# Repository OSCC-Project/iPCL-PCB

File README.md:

# iPCL-PCB

PCB design assets for the iPCL project (OSCC).

## Designs

| File | Description |
|------|-------------|
| `designs/ProDoc_Schematic1_2_2026-08-04.epro2` | Schematic (ProDoc) |
| `designs/ProDoc_PCB1_2_2026-08-04.epro2` | PCB layout (ProDoc) |
| `designs/Netlist_Schematic1_2_2026-08-04.net` | Netlist |
| `designs/Netlist_Schematic1_2_2026-08-04.tel` | Netlist (TEL) |
| `designs/3D_PCB1_2_2026-08-04.step` | 3D STEP model |
| `designs/典型电路样例 lxq.xlsx` | Typical circuit sample list |

## License

See repository license once published under [OSCC-Project](https://github.com/OSCC-Project).

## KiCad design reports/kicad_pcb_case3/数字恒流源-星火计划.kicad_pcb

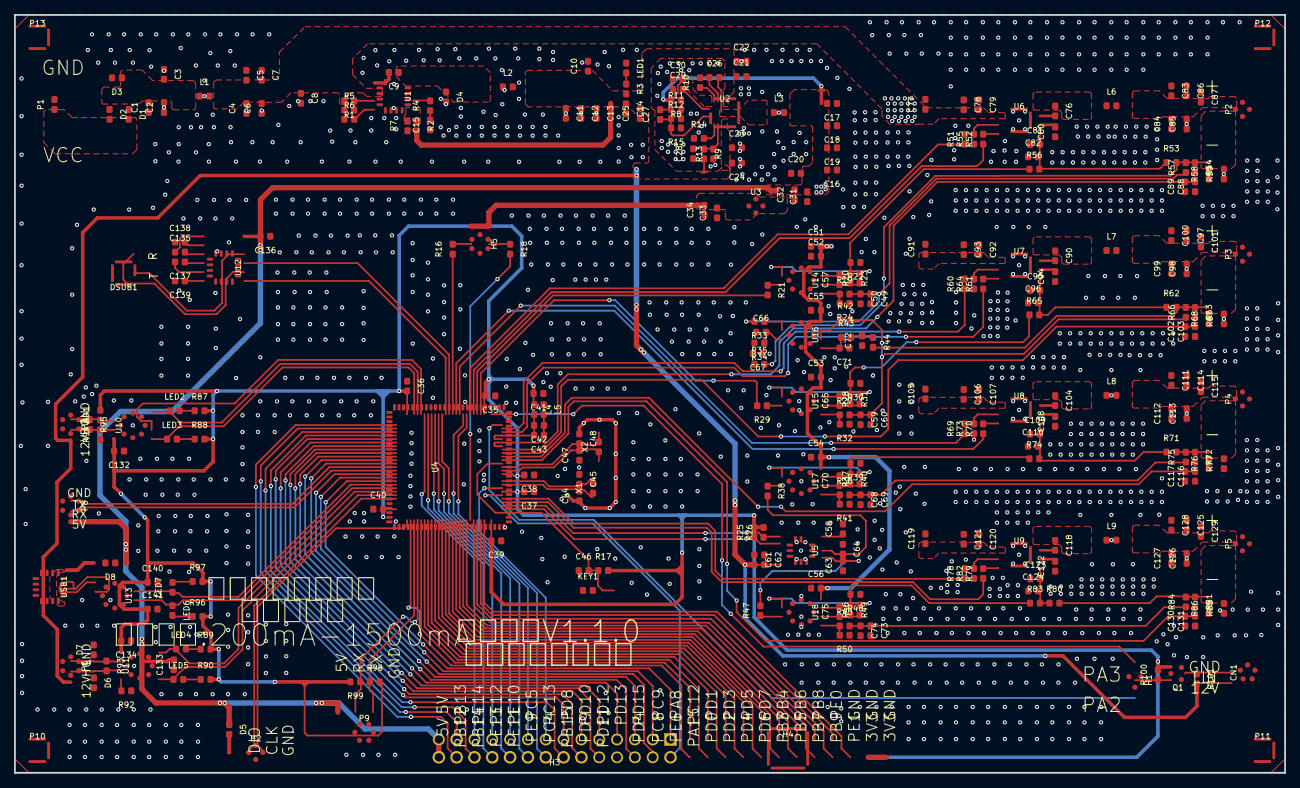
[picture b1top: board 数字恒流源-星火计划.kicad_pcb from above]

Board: 4 copper layers, 181.0 x 108.0 mm, 309 parts (0 on the bottom side), 202 nets.

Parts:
C1, C2, C3, C4, C5, C6, C7, C11, C12, C13, C20, C21, C22, C23, C24, C25, C78, C79, C83, C84, C85, C86, C92, C93, C97, C98, C99, C100, C106, C107, C111, C112, C113, C114, C120, C121, C125, C126, C127, C128: e96d277d502042fc9173dc780b78fded
C8, C10, C77, C91, C105, C119: 3df9e599d0414917abcfb16e8e83100c
C9, C14, C15, C26, C27, C28, C29, C30, C32, C34, C35, C36, C37, C38, C39, C40, C41, C42, C43, C44, C45, C46, C47, C48, C49, C50, C51, C52, C53, C54, C55, C56, C57, C59, C60, C61, C62, C63, C64, C65, C66, C67, C68, C69, C70, C71, C72, C73, C74, C75, C76, C81, C87, C88, C89, C90, C95, C101, C102, C103, C104, C109, C115, C116, C117, C118, C123, C129, C130, C131, C132, C133, C134, C135, C136, C137, C138, C139, C140, C141: d43c57dabb074695b83f6c5ece9dfbc0
C16, C17, C18, C19: e56b4b6283c34385a23001d04bdf17c1
C31, C33, C58, C80, C82, C94, C96, C108, C110, C122, C124: c673d96c40fd49d18ec06c7601c92dee
CN1: a155eebd11e84e1b8b024e8a2b644f7c
D1, D2, D4: 0a0f236fe8304a52bd9bdc3168ba5b28
D3: 9fa78a6e65464e84b8166c84df01a9b8
D5: 2547b60979ec48ccb58c8144d461688f
D6, D7: 46aef89c2ae14484b496801413db11b2
D8: e597590073b7445ca00a9ed5e97cb752
DSUB1: 78054052cb354456aace148f6c3cc170
H1: f34bd33e4d4445a5802cd165ac7db6a0
H2: 9bbbde084a784c84807c689c63475ff3
H3: HDR-TH_28P-P2.54-V-M-R2-C14-S2.54
H4: b2b0b07d56214ac1871de7bf8444b3e2
H5: 04ee0fc8522d435ca4a7133ac1a03957
KEY1: 75f994e15e4b4705a0cd7fbbf4cb88f6
L1, L3: 7a3106fce6fb4d24a5d8c505b0f16d28
L2: d79fc7e4c69e40d6bbdcca2b16fd6ab7
L4, L5: 94c10427d993400cabd1931facc6c4e7
L6, L7, L8, L9: 77b0f7ede56b4dcfb1157d3356b61a4a
LED1: a4245ea0d56f43769908e56462f68a50
LED2, LED4, LED6: d8977324455a43e486a51f69c3e0ebec
LED3, LED5, LED7: 25dc596e01f04ad598871f672402e74f
P1: d3b133b6040647e38816b94f9ba00644
P2, P3, P4, P5: da8421657a814e87b940b5aa13b556fc
P6, P7, P8: 83454cd1be3d49f9884bd864f2696c48
P9: 979c51a9f13843869e344959d279179d
P10: e1
P11: e2
P12: e3
P13: e4
Q1: de940261882f4488b7b39f0608cc75b8
R1, R2, R3, R4, R5, R6, R7, R8, R9, R10, R11, R12, R13, R14, R15, R16, R17, R18, R19, R20, R21, R22, R23, R24, R25, R26, R27, R28, R29, R30, R31, R32, R33, R34, R35, R36, R37, R38, R39, R40, R41, R42, R43, R44, R45, R46, R47, R48, R49, R50, R51, R52, R53, R54, R55, R56, R57, R60, R61, R62, R63, R64, R65, R66, R69, R70, R71, R72, R73, R74, R75, R78, R79, R80, R81, R82, R83, R84, R87, R88, R89, R90, R91, R92, R93, R94, R95, R96, R97, R98, R99, R100, R101: 97e74b7eaa194d86a84b11afd10d1db6
R58, R59, R67, R68, R76, R77, R85, R86: e2875615904e4c0fb259dee520acdfc9
U1: 6fabf947df0c4fde850b752d92a51271
U2: a9375d3fad0b4532ab93fa5967bcc4a1
U3: e588
U4: d3e2155f303d4bbeb146d6ce685b2e71
U5: 736a64b580174d1c832d93b39a210a76
U6, U7, U8, U9: 44bbd12348cb4d0bb938cab1caea8490
U10, U11: 3e52bda23858410b9045661c1d3f8f34
U12: 7232114b47ae4b61b31a13f06dd4fb8b
U13: 5eb26e991ec84f6a84c788ccaff1a8fd
U14, U15, U16, U17, U18: 80882f6c592b4c3eaba774a19986bbd4
USB1: b93ab470b72646d5a0febb31a28badb1
X1: 2c7c0796d64844b4a447b170184cea1b
X2: 2c96f03abeb54cce82ac8a97d7e0bb2f

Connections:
3.3V: C33.2, C34.2, C35.2, C36.2, C37.2, C38.2, C39.2, C40.2, C41.2, C132.2, C134.2, C140.1, C141.1, H4.21, H4.23, H5.1, H5.2, L4.1, Q1.1, R17.2, R25.2, R26.2, R87.2, R88.2, R89.2, R90.2, R91.2, R96.2, R97.2, R98.2, R99.2, R100.2, U3.2, U3.4, U4.6, U4.11, U4.28, U4.50, U4.75, U4.100, U10.8, U11.5, U13.5, U13.8
3AV3: C42.2, C43.2, L4.2, U4.21, U4.22
12V: C10.1, C11.1, C12.1, C13.1, C14.1, C21.1, C22.1, C23.1, C24.2, C25.2, C61.2, C62.2, CN1.3, L2.2, P6.4, P7.4, R2.2, R3.2, R9.2, R101.2, U2.8, U2.12, U5.5
232RX: U4.38, U12.13
232TX: U4.39, U12.11
485R/D: U4.46, U10.2, U10.3
485RX: LED3.1, U4.48, U10.1
485TX: LED2.2, U4.47, U10.4
$1N418: C1.2, C2.2, C3.2, D1.1, D2.1, D3.1, L1.1
$1N617: D1.2, D2.2, P1.1
$1N1409: C9.2, U1.1
$1N1410: R6.2, U1.4
$1N1411: R1.1, R5.2, U1.3
$1N1413: C9.1, D4.1, L2.1, U1.8
$1N1414: R4.2, U1.6
$1N1415: C15.2, R4.1
$1N1416: R2.1, R7.2, U1.5
$1N1418: LED1.2, R3.1
$1N5123: R14.2, U2.6
$1N5196: C29.2, U2.2
$1N5290: C28.2, R9.1, R13.2, U2.7
$1N5484: R10.1, U2.14
$1N5522: C26.1, R10.2, U2.13
$1N5536: C26.2, L3.1, U2.10
$1N5782: C27.1, R12.1, R15.2, U2.4
$1N5836: R8.1, R11.2, R12.2
$1N7221: C27.2, R11.1
$2N3317: D5.2, H2.1
$2N11998: H5.3, R16.2
$2N12002: H5.4, R18.1
$3N1631: R29.1, U15.3
$3N1633: R28.2, U15.1, U15.2
$3N1634: R27.1, R32.2, U15.5
$3N1635: C65.1, R28.1, R31.2, U15.6
$3N2285: R21.1, U14.3
$3N2287: R20.2, U14.1, U14.2
$3N2288: R19.1, R24.2, U14.5
$3N2289: C57.1, R20.1, R23.2, U14.6
$3N2780: R38.1, U17.3
$3N2782: R37.2, U17.1, U17.2
$3N2783: R36.1, R41.2, U17.5
$3N2784: C70.1, R37.1, R40.2, U17.6
$3N3275: R47.1, U18.3
$3N3277: R46.2, U18.1, U18.2
$3N3278: R45.1, R50.2, U18.5
$3N3279: C75.1, R46.1, R49.2, U18.6
$3N3905: C58.1, U5.10
$3N7685: C67.2, R34.2, R35.1
$3N7768: C66.2, R34.1, U16.3
$3N11469: R33.1, U16.1, U16.2
$3N11683: C72.2, R43.2, R44.1
$3N11684: C71.2, R43.1, U16.5
$3N11689: R42.1, U16.6, U16.7
$4N962: R51.2, R55.2, U6.3
$4N963: C76.2, U6.7
$4N964: C80.2, U6.6
$4N965: C76.1, L6.1, U6.8
$4N974: C81.2, C82.2, R53.1, R56.2, U6.5
$4N977: C83.2, C84.2, C85.2, C86.2, C87.2, L6.2, P2.1
$4N2358: R52.2, U6.4
$4N3766: R60.2, R64.2, U7.3
$4N3770: C90.2, U7.7
$4N3771: C94.2, U7.6
$4N3772: C90.1, L7.1, U7.8
$4N3813: C95.2, C96.2, R62.1, R65.2, U7.5
$4N3822: C97.2, C98.2, C99.2, C100.2, C101.2, L7.2, P3.1
$4N3830: R61.2, U7.4
$4N4765: R69.2, R73.2, U8.3
$4N4769: C104.2, U8.7
$4N4770: C108.2, U8.6
$4N4771: C104.1, L8.1, U8.8
$4N4812: C109.2, C110.2, R71.1, R74.2, U8.5
$4N4821: C111.2, C112.2, C113.2, C114.2, C115.2, L8.2, P4.1
$4N4829: R70.2, U8.4
$4N5764: R78.2, R82.2, U9.3
$4N5768: C118.2, U9.7
$4N5769: C122.2, U9.6
$4N5770: C118.1, L9.1, U9.8
$4N5811: C123.2, C124.2, R80.1, R83.2, U9.5
$4N5820: C125.2, C126.2, C127.2, C128.2, C129.2, L9.2, P5.1
$4N5828: R79.2, U9.4
$4N8306: P4.2, R71.2, R72.1, R75.2, R76.2, R77.2
$4N8351: P5.2, R80.2, R81.1, R84.2, R85.2, R86.2
$5N533: R92.2, U11.8
$5N542: LED4.1, R89.1
$5N543: LED5.2, R90.1
$5N1498: LED2.1, R87.1
$5N1499: LED3.2, R88.1
$5N2510: U13.1, USB1.6, USB1.8
$5N2511: U13.2, USB1.5, USB1.7
$5N2517: D8.2, USB1.2, USB1.11
$5N2522: LED6.1, R96.1
$5N2523: LED7.2, R97.1
$5N4046: C135.1, U12.1
$5N4047: C135.2, U12.3
$5N4048: C137.1, U12.4
$5N4049: C137.2, U12.5
$5N4050: C139.1, U12.6
$5N4055: C138.2, U12.2
$5N4058: DSUB1.2, U12.12
$5N4059: DSUB1.3, U12.14
+5V: C16.2, C17.2, C18.2, C19.2, C20.2, C30.2, C31.2, C32.2, C51.2, C52.2, C53.2, C54.2, C55.2, C56.2, C133.2, C136.2, D5.1, D8.1, H3.27, H3.28, L3.2, P8.4, P9.1, R8.2, U2.1, U3.3, U11.3, U12.16, U14.8, U15.8, U16.8, U17.8, U18.8
A: P7.2, R91.1, R95.1, U10.6
ADC1: C88.2, C89.2, R54.2, U4.18
ADC2: C102.2, C103.2, R63.2, U4.17
ADC3: C116.2, C117.2, R72.2, U4.16
ADC4: C130.2, C131.2, R81.2, U4.15
AGND: C42.1, C43.1, L5.2, U4.19, U4.20
B: P7.3, R94.2, R95.2, U10.7
BOOT0: R18.2, U4.94
BOOT1: R16.1, U4.37
CANH: D6.1, P6.3, R93.2, U11.7
CANL: D7.1, P6.2, R93.1, U11.6
CANRXD: LED4.2, U4.70, U11.4
CANTXD: LED5.1, U4.71, U11.1
DACINT1: R21.2, U4.30
DACINT2: R29.2, U4.29
DACINT3: C64.2, R38.2, U5.8
DACINT4: C63.2, R47.2, U5.7
FA1: R52.1, U4.31
FA2: R61.1, U4.23
FA3: R70.1, U4.36
FA4: R79.1, U4.3
FB1: C57.2, R22.2, R23.1, R56.1, U14.7
FB2: C65.2, R30.2, R31.1, R65.1, U15.7
FB3: C70.2, R39.2, R40.1, R74.1, U17.7
FB4: C75.2, R48.2, R49.1, R83.1, U18.7
GND: C1.1, C2.1, C3.1, C4.1, C5.1, C6.1, C7.1, C8.2, C10.2, C11.2, C12.2, C13.2, C14.2, C15.1, C16.1, C17.1, C18.1, C19.1, C20.1, C21.2, C22.2, C23.2, C24.1, C25.1, C28.1, C29.1, C30.1, C31.1, C32.1, C33.1, C34.1, C35.1, C36.1, C37.1, C38.1, C39.1, C40.1, C41.1, C44.1, C45.1, C46.1, C47.1, C48.1, C49.2, C50.2, C51.1, C52.1, C53.1, C54.1, C55.1, C56.1, C58.2, C59.2, C60.2, C61.1, C62.1, C63.1, C64.1, C66.1, C67.1, C68.2, C69.2, C71.1, C72.1, C73.2, C74.2, C77.2, C78.1, C79.1, C80.1, C81.1, C82.1, C83.1, C84.1, C85.1, C86.1, C87.1, C88.1, C89.1, C91.2, C92.1, C93.1, C94.1, C95.1, C96.1, C97.1, C98.1, C99.1, C100.1, C101.1, C102.1, C103.1, C105.2, C106.1, C107.1, C108.1, C109.1, C110.1, C111.1, C112.1, C113.1, C114.1, C115.1, C116.1, C117.1, C119.2, C120.1, C121.1, C122.1, C123.1, C124.1, C125.1, C126.1, C127.1, C128.1, C129.1, C130.1, C131.1, C132.1, C133.1, C134.1, C136.1, C138.1, C139.2, C140.2, C141.2, CN1.1, CN1.4, CN1.5, D3.2, D4.2, D6.2, D7.2, DSUB1.5, DSUB1.10, DSUB1.11, H2.4, H4.20, H4.22, H4.24, H5.5, H5.6, KEY1.1, L5.1, LED1.1, P1.2, P2.3, P2.4, P3.3, P3.4, P4.3, P4.4, P5.3, P5.4, P6.1, P6.5, P6.6, P7.1, P7.5, P7.6, P8.1, P8.5, P8.6, P9.4, P9.5, P9.6, P10.1, P11.1, P12.1, P13.1, R5.1, R6.1, R7.1, R13.1, R14.1, R15.1, R22.1, R24.1, R30.1, R32.1, R39.1, R41.1, R48.1, R50.1, R55.1, R58.1, R59.1, R64.1, R67.1, R68.1, R73.1, R76.1, R77.1, R82.1, R85.1, R86.1, R92.1, R94.1, U1.7, U1.9, U1.e14, U1.e15, U1.e16, U1.e17, U2.3, U2.9, U2.11, U3.1, U4.10, U4.27, U4.49, U4.74, U4.99, U5.3, U5.4, U5.6, U5.9, U5.11, U6.1, U6.9, U7.1, U7.9, U8.1, U8.9, U9.1, U9.9, U10.5, U11.2, U12.15, U13.3, U14.4, U15.4, U16.4, U17.4, U18.4, USB1.1, USB1.12, USB1.13, USB1.14
HMIRX: P9.2, R99.1, U4.79
HMITX: P9.3, R98.1, U4.78
LIN: CN1.2, Q1.3, R101.1
LIN-TR: H1.2, Q1.2, R100.1
NRST: C46.2, KEY1.2, R17.1, U4.14
OUT1+: C49.1, C50.1, R19.2, R33.2, R57.1
OUT2+: C59.1, C60.1, R27.2, R42.2, R66.1
OUT3+: C68.1, C69.1, R36.2, R75.1
OUT4+: C73.1, C74.1, R45.2, R84.1
OUTUP1: P2.2, R35.2, R53.2, R54.1, R57.2, R58.2, R59.2
OUTUP+: P3.2, R44.2, R62.2, R63.1, R66.2, R67.2, R68.2
PA2: H1.3, U4.25
PA3: H1.1, U4.26
PA8: H3.1, U4.67
PA15: H4.1, U4.77
PB3: H4.11, U4.89
PB4: H4.12, U4.90
PB5: H4.13, U4.91
PB6: H4.14, U4.92
PB7: H4.15, U4.93
PB8: H4.16, U4.95
PB9: H4.17, U4.96
PB12: H3.26, U4.51
PB13: H3.25, U4.52
PB14: H3.24, U4.53
PB15: H3.14, U4.54
PC4: H3.16, U4.33
PC5: H3.17, U4.34
PC8: H3.4, U4.65
PC9: H3.3, U4.66
PC12: H4.2, U4.80
PC13: H3.15, U4.7
PD0: H4.3, U4.81
PD1: H4.4, U4.82
PD2: H4.5, U4.83
PD3: H4.6, U4.84
PD4: H4.7, U4.85
PD5: H4.8, U4.86
PD6: H4.9, U4.87
PD7: H4.10, U4.88
PD8: H3.13, U4.55
PD9: H3.12, U4.56
PD10: H3.11, U4.57
PD11: H3.10, U4.58
PD12: H3.9, U4.59
PD13: H3.7, U4.60
PD14: H3.6, U4.61
PD15: H3.5, U4.62
PE0: H4.18, U4.97
PE1: H4.19, U4.98
PE6: H3.2, U4.5
PE9: H3.18, U4.40
PE10: H3.19, U4.41
PE11: H3.20, U4.42
PE12: H3.21, U4.43
PE13: H3.22, U4.44
PE14: H3.23, U4.45
PWM1: R51.1, U4.32
PWM2: R60.1, U4.24
PWM3: R69.1, U4.35
PWM4: R78.1, U4.4
RXD4: P8.3, U4.64
SCLK: R26.1, U4.2, U5.1
SDA: R25.1, U4.1, U5.2
SWCLK: H2.3, U4.76
SWDIO: H2.2, U4.72
TXD4: P8.2, U4.63
USBRXD: LED7.1, U4.68, U13.7
USBTXD: LED6.2, U4.69, U13.6
VCC: C4.2, C5.2, C6.2, C7.2, C8.1, C77.1, C78.2, C79.2, C91.1, C92.2, C93.2, C105.1, C106.2, C107.2, C119.1, C120.2, C121.2, L1.2, R1.2, U1.2, U6.2, U7.2, U8.2, U9.2
X1: C44.2, U4.8, X1.1
X2: C45.2, U4.9, X1.2
X3: C47.2, U4.12, X2.1
X4: C48.2, U4.13, X2.2

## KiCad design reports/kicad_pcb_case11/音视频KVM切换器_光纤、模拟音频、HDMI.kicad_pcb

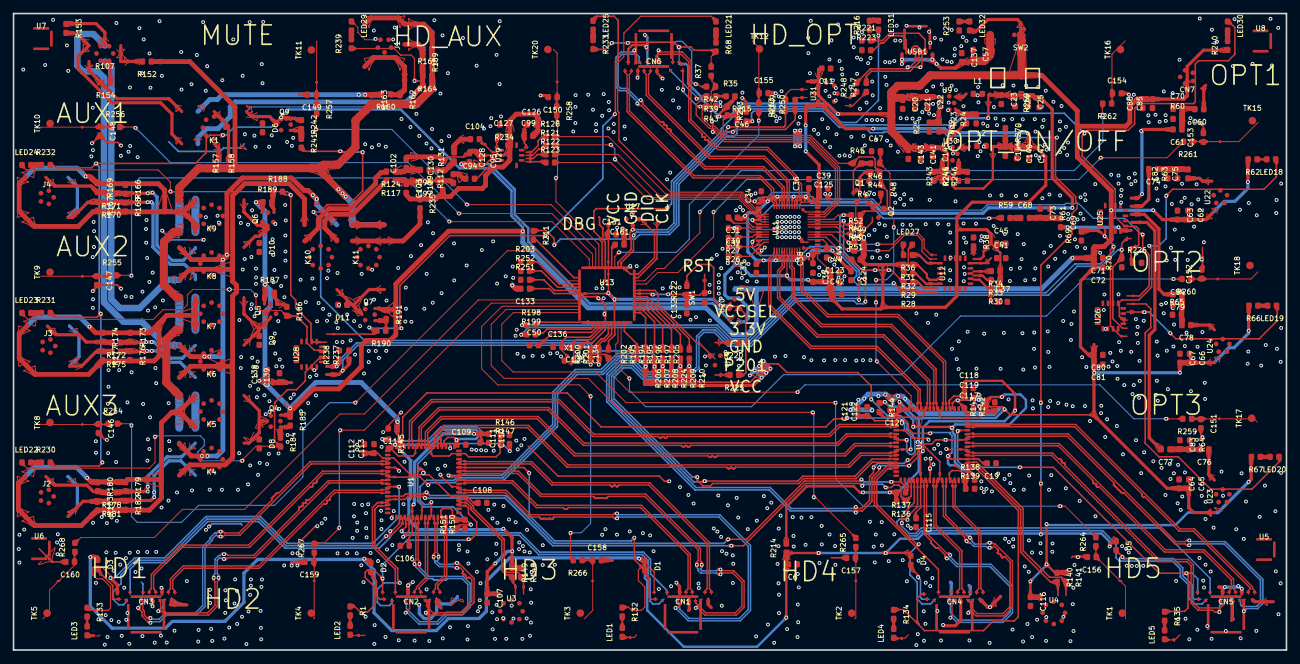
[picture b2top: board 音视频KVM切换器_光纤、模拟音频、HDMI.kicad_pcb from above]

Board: 4 copper layers, 200.0 x 100.0 mm, 398 parts (0 on the bottom side), 323 nets.

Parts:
C6: e144
C11, C50, C57: dc815a0a0b2642b196c3c54ba67a96e7
C19, C60, C61, C63, C64, C65, C68, C69, C73, C75, C76, C77, C79, C80, C81, C83, C84, C85, C86, C131, C137, C154: 9c295d8ac5fc4d838842a31021159ff1
C20: e347
C21: e351
C22: e333
C23: e343
C24: e353
C25: e349
C30: e387
C31: e389
C32: e391
C33: e367
C34, C35, C36, C39, C47, C95, C99, C107, C110, C111, C125, C129, C130: f4b3ad2510624ac5ba87a12a3a8eec41
C37, C41, C45: 0f99d9f41e9847d5a253986aabc90058
C38: e363
C42: e359
C44: e357
C46: e459
C49: e383
C62: e152
C66: e1
C67: e158
C70: e184
C71: e36
C72: e34
C74: e174
C78: e28
C82: e176
C94, C102, C103, C104: 880e0963366643cfb6de0336263f8a40
C97: e303
C98: e305
C106: e294
C108: e302
C109: e306
C112: e318
C113: e322
C114: e326
C115: e330
C116: e334
C117: e338
C118: e342
C119: e346
C120: e350
C121: e354
C122: e358
C123: e134
C124: e136
C126, C127, C128: 092cd929c40b49128514272866187abc
C132: e177
C133: e181
C134: e185
C135: e189
C136: e193
C138: e272
C139: e280
C140: e75
C141: e79
C142: e425
C143: e88
C144: e31
C145: e66
C146: e2340
C147: e2344
C148: e2348
C149: e2352
C150: e2356
C151: e2360
C152: e2364
C153: e2368
C155: e2376
C156: e2380
C157: e2384
C158: e2388
C159: e2392
C160: e2396
C161: e245
CN1: e0
CN2: e92
CN3: e94
CN4: e257
CN5: e259
CN6: e401
CN7: e461
D1: e138
D2: e140
D3: e142
D4: e213
D5: e215
D6: e667
D8: e621
D9: e633
D10: e645
D11: e657
J1, J2, J3, J4: 08305c994c59461b9383666063090ddd
K1: e659
K4, K6, K10, K11: df5bca498b424461b97c80260ad98ac4
K5: e611
K7: e623
K8: e637
K9: e635
L1: e345
L2: e93
LED1: e100
LED2: e98
LED3: e96
LED4: e205
LED5: e209
LED18: e114
LED19: e116
LED20: e118
LED21: e120
LED22: e122
LED23, LED24, LED25, LED27: eecc779babc7491f875c113717232172
LED29: e58
LED30: e50
LED31: e129
LED32: e137
Q1: e447
Q2: e449
Q4: e615
Q5, Q6, Q7: 8f79c3bf922146ff8352e5c5daeb6270
Q9: 8672ae4561fe47b499a65e37c2650851
R1: e214
R22: e339
R23: e337
R24: e335
R25: e341
R26: e309
R27: e311
R28: e433
R29: e435
R30: e355
R31: e327
R32: e325
R33: e379
R34: e321
R35, R45, R47, R52, R59, R60, R61, R64, R65, R68, R70, R112, R121, R122, R123, R126, R131, R134, R146, R147, R157, R158, R163, R164, R165, R166, R169, R170, R173, R174, R176, R177, R179, R180, R182, R183, R184, R186, R187, R188, R189, R190, R193, R194, R195, R196, R197, R198, R199, R205, R215, R216, R221, R230, R231, R232, R233, R235, R239, R247, R248, R249, R250, R252, R253, R263: b3e26573912d4c5ea8af80ab76c41537
R36: e453
R37: e405
R38: e329
R39: e313
R40: e409
R41: e407
R42: e403
R43: e317
R44: e395
R46: e445
R48: e397
R49: e307
R50: e457
R51: e437
R62: e194
R63: e178
R66: e196
R67: e198
R69: e180
R107: 44a4e493004e4ba7a2037dbbbafa0899
R117: e299
R124: e301
R132: e210
R133: e218
R135: e226
R136: e230
R137: e234
R138: e238
R139: e242
R140: e246
R141: e250
R142: e254
R143: e258
R144: e262
R145: e266
R148: e278
R149: e282
R150: e286
R151: e290
R152: e362
R153: e366
R154: e370
R159: e390
R160: e394
R162: e402
R167: e416
R168: e418
R171: e428
R172: e432
R175: e444
R178: e455
R181: e466
R185: e480
R191: e499
R200: e87
R201: e89
R202: e91
R203: e102
R206: e2
R207: e18
R208: e21
R209: e25
R210: e29
R211: e99
R213: e147
R214: e143
R220: e220
R222: e225
R223: e228
R224: e232
R225: e235
R226: e240
R234: e3
R237: e40
R238: e44
R240: e54
R241: e374
R242: e378
R243: e42
R244: e48
R245: e56
R246: e64
R251: e121
R254: e2338
R255: e2342
R256: e2346
R257: e2350
R258: e2354
R259: e2358
R260: e2362
R261: e2366
R262: e2370
R264: e2378
R265: e2382
R266: e2386
R267: e2390
R268: e2394
R269: e533
R270: e511
SW1: e785
SW2: 50167ca068be4d87830589afead6679a
TK1: e33
TK2: e37
TK3: e39
TK4: e41
TK5: e43
TK8: e49
TK9: e51
TK10: e53
TK11: e55
TK12: e104
TK15: e110
TK16: e57
TK17: e59
TK18: e61
TK20: e4
U1, U2: f2533282dbf94f718f9ba5732a66e8b5
U3: ba423903e0dd4732bff89aa70a677ca0
U4: e217
U5, U6, U7, U8: 3f46b0cddeba45cb8b80ee671d4afc18
U9: e331
U11: e443
U12: 4d74d29fca974593b1881c62c09dcb8f
U13: e749
U14: e753
U17: e751
U20: e787
U22, U23, U24: 17a981832f1f4957979ac065c47a430c
U25: b53dace46ad64514ac265dfb7b3ea34a
U26: 5c9a8bd98af14b16802648ab59d36f44
U28: e601
U29: 2131eb8acef24ee3b726ad36e560bb96
U30: e70
U31: 73424880f85843bf863bd4679f44f7ac
USB1: 3d27eabcb12d4f2fbe5f8ebcd63b7c4b
X1: 3731a25e04264d4fa46338222c0f7fde_e789

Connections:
$2N2468: R145.2, U1.43
$2N2585: LED1.2, R132.2
$2N2586: LED2.2, R1.2
$2N2587: LED3.2, R133.2
$2N2715: R146.1, R147.1, U1.38
$2N2717: R150.2, R151.2, U1.14
$2N3249: LED4.2, R134.2
$2N3333: LED5.2, R135.2
$2N4608: R144.2, U2.43
$2N4737: R142.1, R143.1, U2.38
$2N4739: R138.1, R139.1, U2.14
$3N1517: R220.2, U14.3
$3N1519: R225.2, U14.1
$3N1522: LED31.1, R216.2
$3N1635: C57.2, C137.2, SW2.3, USB1.A4B9, USB1.B4A9
$3N5427: R221.2, USB1.A5
$3N5430: R223.2, USB1.B5
$3N6809: R248.1, U31.2
$3N6810: R247.1, U31.1
$3N6939: R250.2, U31.7
$3N6943: R249.2, U31.6
$3N7336: LED32.1, R253.2
$3N7468: C146.1, R254.1, TK8.1
$3N8162: C147.1, R255.1, TK9.1
$3N8239: C148.1, R256.1, TK10.1
$3N8316: C149.1, R257.1, TK11.1
$3N8393: C150.1, R258.1, TK20.1
$3N8475: C151.1, R259.1, TK17.1
$3N8548: C152.1, R260.1, TK18.1
$3N8694: C153.1, R261.1, TK15.1
$3N8767: C154.1, R262.1, TK16.1
$3N8840: C155.1, R263.1, TK12.1
$3N8913: C156.1, R264.1, TK1.1
$3N8990: C157.1, R265.1, TK2.1
$3N9067: C158.1, R266.1, TK3.1
$3N9144: C159.1, R267.1, TK4.1
$3N9221: C160.1, R268.1, TK5.1
$4N2008: LED21.1, U26.7
$4N2009: LED19.1, U26.5
$4N2010: LED18.2, R62.1
$4N2011: LED20.2, R67.1
$4N2026: C60.1, CN7.1
$4N2043: C78.1, U24.3
$4N2062: LED19.2, R66.1
$4N2063: LED18.1, U26.4
$4N2064: LED20.1, U26.6
$4N2065: LED21.2, R68.1
$4N4007: C68.1, R59.2
$4N4034: C68.2, C69.1, C73.2, R61.2
$4N4580: C78.2, C79.1, C84.2, R65.2
$4N4712: C76.2, C77.1, C83.2, R64.2
$4N4717: C76.1, U23.3
$4N4843: C74.1, C75.2, C82.2, R63.2
$4N4848: C75.1, U22.3
$4N5295: C60.2, C61.1, C70.2, R60.2
$4N7989: LED30.2, R240.2
$5N4593: J2.3, R178.2, R180.2
$5N4596: J2.4, R181.2, R183.1
$5N4599: J3.3, R172.2, R174.2
$5N4602: J4.3, R169.2, R171.2
$5N4605: J4.4, R167.1, R170.2
$5N4614: LED25.2, R233.1
$5N4619: LED22.2, R230.1
$5N4642: LED23.2, R231.1
$5N4643: LED24.2, R232.1
$5N4684: R107.1, R107.4, R152.2
$5N4720: J1.3, R159.1, R165.2
$5N4721: J1.4, R160.1, R162.1
$5N4724: D6.1, K1.1, Q9.3, R239.1
$5N4726: J3.4, R175.2, R177.1
$5N4751: K1.9, R159.2, R164.2
$5N4752: K1.4, R160.2, R163.1
$5N4759: Q6.1, R188.1, R189.2
$5N4760: D10.1, K8.1, K9.1, Q6.3
$5N4761: Q7.1, R190.1, R191.2
$5N4763: D11.1, K10.1, K11.1, Q7.3
$5N4765: Q5.1, R186.1, R187.2
$5N4766: D9.1, K6.1, K7.1, Q5.3
$5N4767: Q4.1, R184.1, R185.2
$5N4769: D8.1, K4.1, K5.1, Q4.3
$5N10016: K1.3, R157.2
$5N10052: K1.10, R158.1
$5N17741: LED29.2, R239.2
$5N20118: K1.5, R107.3, R154.2
$5N20122: K1.8, R107.6, R153.2
$5N20303: Q9.1, R241.1, R242.2
$6N2865: R36.1, U12.13
$6N2866: LED27.1, R36.2
$6N2869: R52.1, U11.19
$6N2872: Q1.3, R45.2, R46.2
$6N2879: R29.1, U12.19
$6N2882: R28.1, U12.20
$6N2897: Q2.1, R52.2
$6N2934: R26.1, U11.47
$6N2936: R27.1, U11.45
$6N2987: Q1.1, Q2.3, R48.2
$6N2996: C37.1, R30.2, U12.4
$6N2998: R33.2, U12.5
$6N3000: C41.1, U12.8
$6N3011: R23.2, R24.2, U9.1
$6N3015: L1.1, U9.3
$6N3021: R38.2, U12.10
$6N3022: R32.1, U12.18
$6N3023: R34.2, U12.6
$6N3024: R31.1, U12.17
$6N3484: CN6.15, R39.2
$6N3489: CN6.16, R42.2
$6N6654: C46.2, R40.1, R41.1, R44.1, R45.1, R48.1, R213.2, R215.1
$6N7636: R122.1, U29.2
$6N7639: R121.1, U29.3
$6N7644: R123.1, U29.1
$6N7645: C127.1, U29.6
$6N7646: C99.1, C126.1, U29.5
$6N7650: R126.1, U29.4
$6N7651: C104.2, U29.7
$6N7652: C94.2, U29.10
$6N7653: C104.1, R131.2
$6N7654: C94.1, R112.2
$6N7657: C97.2, C103.1, R117.1
$6N7658: C98.2, C102.1, R124.1
$6N7663: C97.1, C129.2, R112.1
$6N7664: C98.1, C130.1, R131.1
$6N12538: R243.2, R244.1, U30.5
$6N12540: R245.2, R246.2, U30.1
$6N12544: L2.1, U30.3
$6N12582: R22.1, R25.2, U9.5
+1.2V: C23.1, C24.1, C25.1, C31.1, C33.2, C34.1, C36.1, C38.2, C49.1, C124.1, L1.2, R22.2, R269.2, U11.3, U11.9, U11.14, U11.29, U11.34, U11.42
+1.8V_1: C106.1, C110.1, C111.1, U1.5, U1.35
+1.8V_2: C115.1, C118.1, C119.1, U2.5, U2.35
+3.3V: C30.1, C32.2, C35.2, C39.1, C42.1, C44.1, C45.1, C95.2, C123.1, C125.1, C128.2, C140.1, C142.1, C144.1, L2.2, LED27.2, R30.1, R31.2, R32.2, R33.1, R34.1, R49.2, R50.2, R51.2, R244.2, R270.2, U11.6, U11.12, U11.26, U11.44, U11.48, U12.9, U20.3, U29.9, U31.8
+3.3V_1: C108.1, C112.1, C113.1, R145.1, R147.2, R151.1, U1.20, U1.49
+3.3V_2: C19.2, C121.1, C122.1, R138.2, R143.2, R144.1, U2.20, U2.49
+5V: C11.2, C20.1, C21.1, C22.1, C62.2, C63.2, C64.2, C65.2, C66.2, C67.2, C71.2, C72.2, C80.2, C81.2, C85.2, C86.2, C107.1, C109.1, C114.1, C116.1, C117.1, C120.1, C138.1, C139.1, C141.1, C143.1, C145.1, CN6.18, CN7.2, LED32.2, Q4.2, Q5.2, Q6.2, Q7.2, Q9.2, R23.1, R35.2, R37.2, R62.2, R66.2, R67.2, R68.2, R136.2, R137.2, R140.1, R141.1, R148.1, R149.1, R185.1, R187.1, R189.1, R191.1, R213.1, R214.2, R230.2, R231.2, R232.2, R233.2, R240.1, R242.1, R245.1, SW2.2, U1.34, U1.48, U2.34, U2.48, U3.8, U4.8, U9.4, U20.1, U22.1, U23.1, U24.1, U25.16, U26.16, U28.16, U30.4, U31.5
AGND: C95.1, C99.2, C102.2, C103.2, C126.2, C127.2, C128.1, C129.1, C130.2, R234.1, R235.1, U29.8
AUXIN1_L: K4.9, R181.1, R182.1
AUXIN1_R: K4.4, R178.1, R179.2
AUXIN2_L: K6.9, R175.1, R176.1
AUXIN2_R: K6.4, R172.1, R173.2
AUXIN3_L: K8.9, R168.1, R170.1
AUXIN3_R: K8.4, R166.2, R171.1
AUXIN4_L: K10.9, R124.2
AUXIN4_R: K10.4, R117.2
AUXOUT_L: K4.8, K6.8, K8.8, K10.8, R107.2, R154.1
AUXOUT_R: K4.5, K6.5, K8.5, K10.5, R107.5, R153.1
AUX_A: R200.1, R237.1, U28.2
AUX_B: R201.1, R238.1, U28.3
DN: R248.2, USB1.A7, USB1.B7
DP: R247.2, USB1.A6, USB1.B6
EN1: LED22.1, R184.2, U28.4
EN2: LED23.1, R186.2, U28.5
EN3: LED24.1, R188.2, U28.6
EN4: LED25.1, R190.2, U28.7
GND: C6.1, C11.1, C19.1, C20.2, C21.2, C22.2, C23.2, C24.2, C25.2, C30.2, C31.2, C32.1, C33.1, C34.2, C35.1, C36.2, C37.2, C38.1, C39.2, C41.2, C42.2, C44.2, C45.2, C46.1, C47.1, C49.2, C50.1, C57.1, C62.1, C63.1, C64.1, C65.1, C66.1, C67.1, C70.1, C71.1, C72.1, C73.1, C80.1, C81.1, C82.1, C83.1, C84.1, C85.1, C86.1, C106.2, C107.2, C108.2, C109.2, C110.2, C111.2, C112.2, C113.2, C114.2, C115.2, C116.2, C117.2, C118.2, C119.2, C120.2, C121.2, C122.2, C123.2, C124.2, C125.2, C131.2, C132.1, C133.2, C134.1, C135.1, C136.1, C137.1, C138.2, C139.2, C140.2, C141.2, C142.2, C143.2, C144.2, C145.2, C146.2, C147.2, C148.2, C149.2, C150.2, C151.2, C152.2, C153.2, C154.2, C155.2, C156.2, C157.2, C158.2, C159.2, C160.2, C161.2, CN1.2, CN1.5, CN1.8, CN1.11, CN1.17, CN1.20, CN2.2, CN2.5, CN2.8, CN2.11, CN2.17, CN2.20, CN3.2, CN3.5, CN3.8, CN3.11, CN3.17, CN3.20, CN4.2, CN4.5, CN4.8, CN4.11, CN4.17, CN4.20, CN5.2, CN5.5, CN5.8, CN5.11, CN5.17, CN5.20, CN6.2, CN6.5, CN6.8, CN6.11, CN6.17, CN6.20, CN7.3, D6.2, D8.2, D9.2, D10.2, D11.2, K1.12, K4.12, K5.12, K6.12, K7.12, K8.12, K9.12, K10.12, K11.12, LED1.1, LED2.1, LED3.1, LED4.1, LED5.1, LED29.1, Q1.2, Q2.2, R24.1, R25.1, R26.2, R27.2, R38.1, R43.1, R47.1, R60.1, R61.1, R63.1, R64.1, R65.1, R69.1, R70.1, R139.2, R142.2, R146.2, R150.1, R206.2, R207.2, R208.2, R209.2, R210.2, R216.1, R220.1, R221.1, R223.1, R224.2, R226.2, R234.2, R237.2, R238.2, R243.1, R246.1, R253.1, R269.1, R270.1, SW1.1, U1.8, U1.23, U1.33, U1.52, U2.8, U2.23, U2.33, U2.52, U3.1, U3.2, U3.3, U3.4, U4.1, U4.2, U4.3, U4.4, U5.1, U6.1, U7.1, U8.1, U9.2, U11.13, U11.43, U11.49, U12.7, U13.6, U13.31, U13.43, U17.2, U22.2, U23.2, U24.2, U25.8, U26.1, U26.8, U28.1, U28.8, U30.2, U31.3, USB1.1, USB1.2, USB1.3, USB1.4, USB1.A1B12, USB1.B1A12
GND1: J2.2, K5.4, K5.9, R179.1, R180.1, R182.2, R183.2
GND2: J3.2, K7.4, K7.9, R173.1, R174.1, R176.2, R177.2
GND3: J4.2, K9.4, K9.9, R166.1, R167.2, R168.2, R169.1
GND4: K11.4, K11.9, R235.2
HDMIEN_1: R193.1, R206.1, U1.55
HDMIEN_2: R194.1, R207.1, U1.11
HDMIEN_3: R195.1, R208.1, U1.26
HDMIEN_4: R197.1, R209.1, U2.11
HDMIEN_5: R205.1, R210.1, U2.26
HDMIEN_MID: R196.1, R224.1, U2.55
HDMIIN5V: C6.2, D1.1, D2.1, D3.1, D4.1, D5.1, R214.1, R215.2
HDMIRXDET: R44.2, R47.2, U11.20
HDMITX0N: CN6.9, U11.30
HDMITX0P: CN6.7, U11.31
HDMITX1N: CN6.6, U11.32
HDMITX1P: CN6.4, U11.33
HDMITX2N: CN6.3, U11.35
HDMITX2P: CN6.1, U11.36
HDMITXCN: CN6.12, U11.27
HDMITXCP: CN6.10, U11.28
HDMITXHPD: CN6.19, R43.2, U11.23
HDMITXSCL: R35.1, R39.1, U11.25
HDMITXSDA: R37.1, R42.1, U11.24
HD_SPDIFO: R59.1, U11.41
I2S_MCLK: R126.2, U11.37
I2S_SCLK: R122.2, U11.38
I2S_SD: R123.2, U11.40
I2S_SW: R121.2, U11.39
INT: R28.2, U11.46
OPT_A: R69.2, R198.1, U25.14, U26.2
OPT_B: R70.2, R199.1, U25.2, U26.3
OPT_EN: LED30.1, R211.1, R226.1, U25.1
OUTGND: J1.2, K5.5, K5.8, K7.5, K7.8, K9.5, K9.8, K11.5, K11.8, R152.1, R157.1, R158.2, R162.2, R163.2, R164.1, R165.1
P000: R264.2, U13.48
P001: R265.2, U13.47
P002: R266.2, U13.46
P010: R267.2, U13.45
P011: R268.2, U13.44
P012: R251.2, U13.41
P013: R252.2, U13.40
P014: R203.2, U13.39
P015: R254.2, U13.38
P100: R255.2, U13.36
P101: R256.2, U13.35
P102: R257.2, U13.34
P103: R258.2, U13.33
P104: LED31.2, U13.32
P109: R250.1, U13.26
P110: R249.1, U13.27
P111: R263.2, U13.28
P112: C161.1, U13.29
P201: U13.20, U14.2
P206: R205.2, U13.18
P207: R197.2, U13.17
P208: R196.2, U13.16
P212: R201.2, U13.8
P213: R200.2, U13.7
P214: C135.2, U13.5, X1.1
P215: C136.2, U13.4, X1.2
P301: R262.2, U13.23
P302: R261.2, U13.22
P400: R198.2, U13.1
P401: R199.2, U13.2
P407: R202.2, U13.12
P408: R260.2, U13.11
P409: R259.2, U13.10
P500: R211.2, U13.37
P913: R195.2, U13.15
P914: R194.2, U13.14
P915: R193.2, U13.13
RES: C132.2, R222.1, SW1.2, U13.19
RSTN: R29.2, R51.1, U11.15
RX1_5V: CN1.18, D1.2
RX1_CLK+: CN1.10, U1.22
RX1_CLK-: CN1.12, U1.21
RX1_D0+: CN1.7, U1.25
RX1_D0-: CN1.9, U1.24
RX1_D1+: CN1.4, U1.28
RX1_D1-: CN1.6, U1.27
RX1_D2+: CN1.1, U1.31
RX1_D2-: CN1.3, U1.30
RX1_HPD: CN1.19, R132.1, U1.29
RX1_SCL: CN1.15, U1.3
RX1_SDA: CN1.16, U1.4
RX2_5V: CN2.18, D2.2
RX2_CLK+: CN2.10, U1.7
RX2_CLK-: CN2.12, U1.6
RX2_D0+: CN2.7, U1.10
RX2_D0-: CN2.9, U1.9
RX2_D1+: CN2.4, U1.13
RX2_D1-: CN2.6, U1.12
RX2_D2+: CN2.1, U1.16
RX2_D2-: CN2.3, U1.15
RX2_HPD: CN2.19, R1.1, U1.17
RX2_SCL: CN2.15, U1.63
RX2_SDA: CN2.16, U1.64
RX3_5V: CN3.18, D3.2
RX3_CLK+: CN3.10, U1.51
RX3_CLK-: CN3.12, U1.50
RX3_D0+: CN3.7, U1.54
RX3_D0-: CN3.9, U1.53
RX3_D1+: CN3.4, U1.57
RX3_D1-: CN3.6, U1.56
RX3_D2+: CN3.1, U1.60
RX3_D2-: CN3.3, U1.59
RX3_HPD: CN3.19, R133.1, U1.58
RX3_SCL: CN3.15, U1.1
RX3_SDA: CN3.16, U1.2
RX4_5V: CN4.18, D4.2
RX4_CLK+: CN4.10, U2.7
RX4_CLK-: CN4.12, U2.6
RX4_D0+: CN4.7, U2.10
RX4_D0-: CN4.9, U2.9
RX4_D1+: CN4.4, U2.13
RX4_D1-: CN4.6, U2.12
RX4_D2+: CN4.1, U2.16
RX4_D2-: CN4.3, U2.15
RX4_HPD: CN4.19, R134.1, U2.17
RX4_SCL: CN4.15, U2.63
RX4_SDA: CN4.16, U2.64
RX5_5V: CN5.18, D5.2
RX5_CLK+: CN5.10, U2.22
RX5_CLK-: CN5.12, U2.21
RX5_D0+: CN5.7, U2.25
RX5_D0-: CN5.9, U2.24
RX5_D1+: CN5.4, U2.28
RX5_D1-: CN5.6, U2.27
RX5_D2+: CN5.1, U2.31
RX5_D2-: CN5.3, U2.30
RX5_HPD: CN5.19, R135.1, U2.29
RX5_SCL: CN5.15, U2.3
RX5_SDA: CN5.16, U2.4
SCL: R50.1, U11.16, U12.12
SCL_1: R149.2, U1.18, U3.6
SCL_2: R140.2, U2.18, U4.6
SDA: R49.1, U11.17, U12.11
SDA_1: R148.2, U1.19, U3.5
SDA_2: R141.2, U2.19, U4.5
SPDIFIN1: C74.2, U25.6
SPDIFIN2: C79.2, U25.5
SPDIFIN3: C77.2, U25.4
SPDIFIN4: C69.2, U25.3
SPDIFO: C61.2, U25.7
SWCLK: U13.24, U17.4
SWDIO: U13.25, U17.3
TX0_CLK+: U1.44, U2.51
TX0_CLK-: U1.45, U2.50
TX0_D0+: U1.41, U2.54
TX0_D0-: U1.42, U2.53
TX0_D1+: U1.39, U2.57
TX0_D1-: U1.40, U2.56
TX0_D2+: U1.36, U2.60
TX0_D2-: U1.37, U2.59
TX0_HPD: U1.47, U2.58
TX0_SCL: R137.1, U1.61, U2.1
TX0_SDA: R136.1, U1.62, U2.2
TX_CLK+: U2.44, U11.2
TX_CLK-: U2.45, U11.1
TX_D0+: U2.41, U11.5
TX_D0-: U2.42, U11.4
TX_D1+: U2.39, U11.8
TX_D1-: U2.40, U11.7
TX_D2+: U2.36, U11.11
TX_D2-: U2.37, U11.10
TX_HPD: C47.2, R46.1, U2.47
TX_SCL: R41.2, U2.61, U11.22
TX_SDA: R40.2, U2.62, U11.21
VCC: C131.1, C133.1, C134.2, R222.2, R225.1, U13.9, U13.30, U13.42, U17.1, U20.2
VCL: C50.2, U13.3
VOL_MUTE: R202.1, R241.2

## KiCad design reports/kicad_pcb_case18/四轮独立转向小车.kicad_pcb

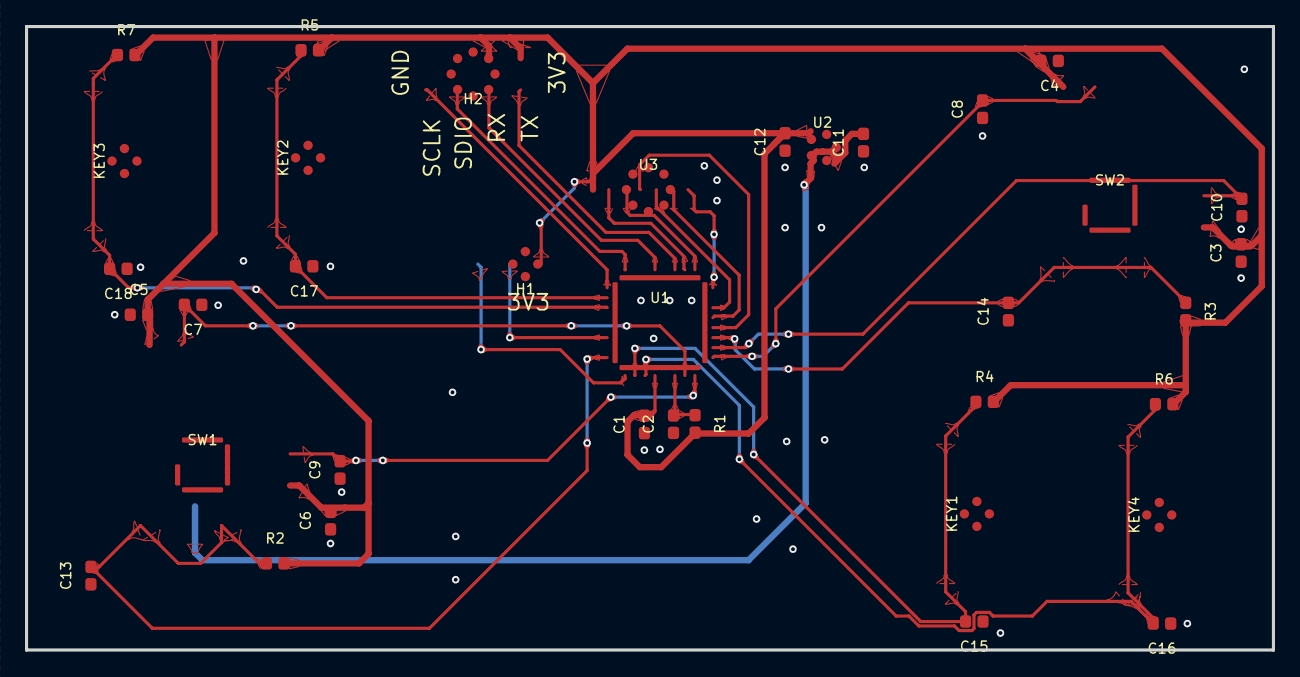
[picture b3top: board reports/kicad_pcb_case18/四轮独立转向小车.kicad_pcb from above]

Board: 4 copper layers, 100.0 x 50.0 mm, 37 parts (1 on the bottom side), 26 nets.

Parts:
BT1: d876c9e8abfa46a4bbed8f59aa63afaf
C1, C2, C3, C4, C5, C6, C13, C14, C15, C16, C17, C18: 16cbe5f9e76c4855a78e246f52ac3570
C7, C8, C9, C10, C11, C12: 741784fa20ad4beab9dd8b8cbce97607
H1: 18a79955d83244dfaf45ce8ee3e04863
H2: 648849d55ce94beca6d893b0b88daeda
KEY1, KEY2, KEY3, KEY4: a10471bacaf64bc086e7f3f1ee381836
R1, R2, R3, R4, R5, R6, R7: 1996b2fb973e40a184d52a2e5e193df3
SW1, SW2: c8c8571dd8cf4ff49b1d53a434a5e7e1
U1: 396507a046414973906a8dc2eef0e817
U2: 1c877eef906c458a8606b5978f0aeb3b
U3: 91d99640c4a348eb8a20141652c3be94

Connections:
3V3: C1.2, C3.2, C4.2, C5.2, C6.2, C12.2, H1.2, H2.1, H2.3, R1.2, R2.2, R3.2, R4.2, R5.2, R6.2, R7.2, SW1.1, SW1.6, SW2.1, SW2.6, U1.4, U2.5, U3.1
BAT: BT1.2, C11.2, U2.1, U2.3
CE: U1.18, U3.2
CSN: U1.17, U3.3
GND: BT1.1, C1.1, C2.1, C3.1, C4.1, C5.1, C6.1, C7.1, C8.1, C9.1, C10.1, C11.1, C12.1, C13.1, C14.1, C15.1, C16.1, C17.1, C18.1, H1.1, H2.5, H2.7, KEY1.1, KEY1.2, KEY2.1, KEY2.2, KEY3.1, KEY3.2, KEY4.1, KEY4.2, SW1.3, SW1.4, SW1.7, SW1.8, SW1.9, SW1.10, SW1.c, SW1.d, SW2.3, SW2.4, SW2.7, SW2.8, SW2.9, SW2.10, SW2.c, SW2.d, U1.5, U2.2, U3.8
I2C_SCL: H1.3, U1.30
I2C_SDA: H1.4, U1.1
IRQ: U1.16, U3.7
KEY1: C15.2, KEY1.3, KEY1.4, R4.1, U1.2
KEY2: C16.2, KEY4.3, KEY4.4, R6.1, U1.3
KEY3: C18.2, KEY3.3, KEY3.4, R7.1, U1.27
KEY4: C17.2, KEY2.3, KEY2.4, R5.1, U1.26
NRST: C2.2, R1.1, U1.6
SPI_MISO: U1.13, U3.6
SPI_MOSI: U1.14, U3.5
SPI_SCK: U1.12, U3.4
SW1_X: C7.2, SW1.5, U1.7
SW1_Y: C9.2, SW1.2, U1.8
SW1_Z: C13.2, R2.1, SW1.a, SW1.b, U1.32
SW2_X: C8.2, SW2.5, U1.9
SW2_Y: C10.2, SW2.2, U1.10
SW2_Z: C14.2, R3.1, SW2.a, SW2.b, U1.11
SWCLK: H2.8, U1.25
SWDIO: H2.6, U1.24
USART1_RX: H2.4, U1.21
USART1_TX: H2.2, U1.19
